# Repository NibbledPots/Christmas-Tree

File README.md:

# Christmas-Tree
Fun christmas tree PCB ornament with LEDs
* Base is roughly 5cm and its about 6.5cm tall
* Has a nice hole in it to make it an ornament

Used to be series, turns out that doesn't work so now its parallel. I don't really know how to nicely route parallel circuits so it looks ugly and **might not work**, maybe I'll try again next christmas

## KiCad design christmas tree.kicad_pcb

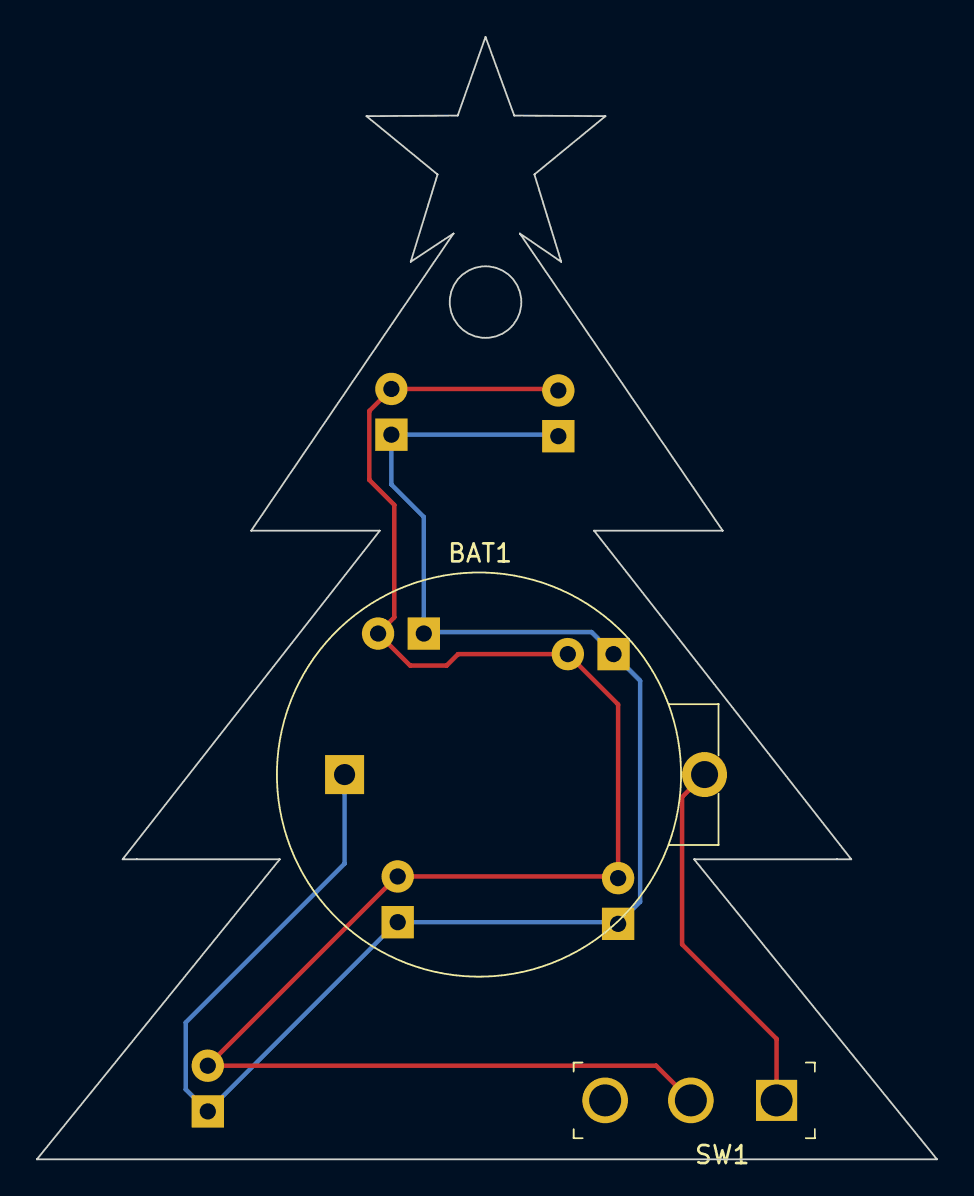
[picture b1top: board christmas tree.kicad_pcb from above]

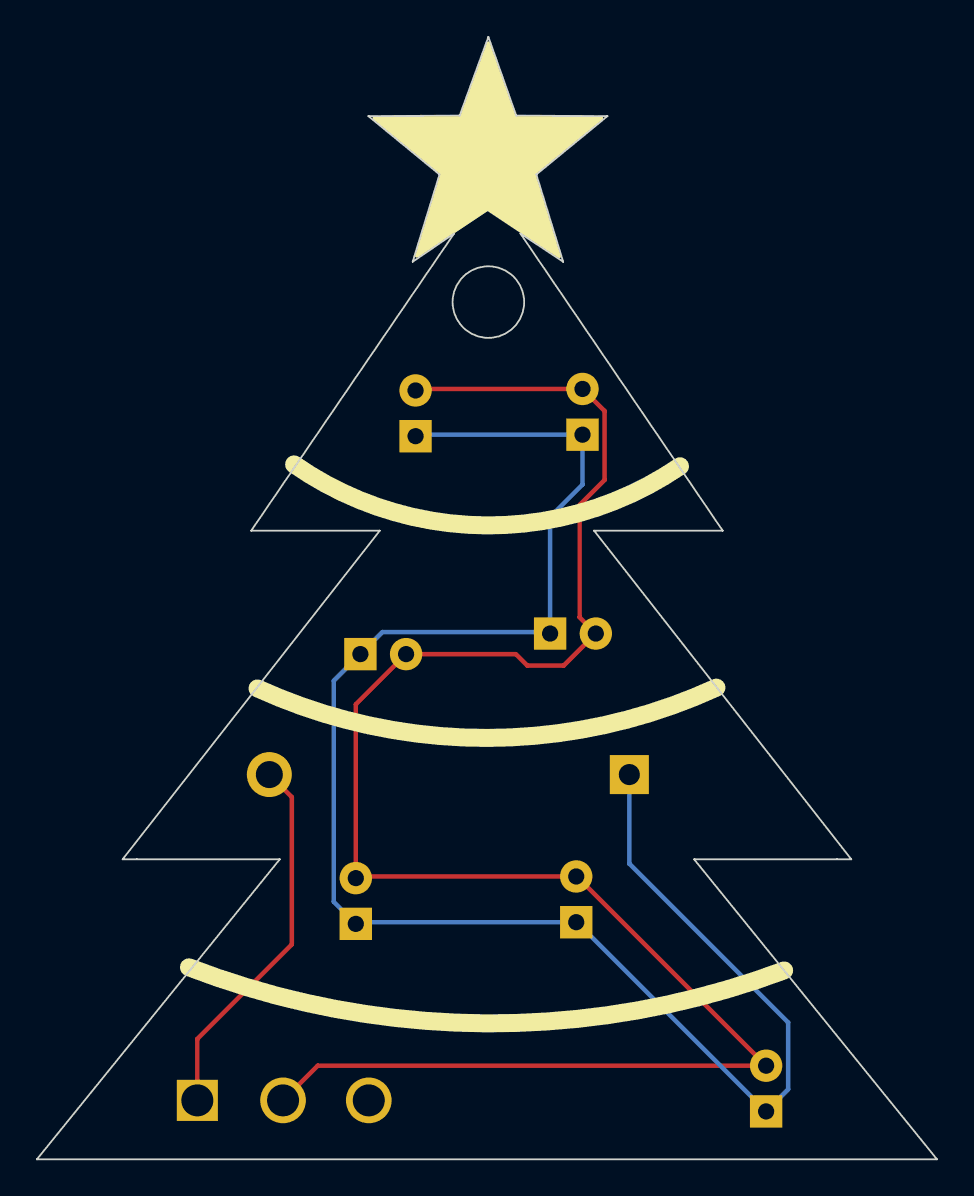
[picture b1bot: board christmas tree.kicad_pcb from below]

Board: 2 copper layers, 50.0 x 62.4 mm, 9 parts (7 on the bottom side), 3 nets.

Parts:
BAT1: BS-7; Battery_Holder_Coin_2032_BS-7
D1, D2, D3, D4, D6, D7: LED; LED_D5.0mm
Dr: LED; LED_D5.0mm
SW1: SW_SPST; Switch_Slide_11.6x4mm_EG1218

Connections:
unnamed: BAT1.Neg, D1.1 (K), D2.1 (K), D3.1 (K), D4.1 (K), D6.1 (K), D7.1 (K), Dr.1 (K)
unnamed: BAT1.Pos, SW1.1 (A)
unnamed: D1.2 (A), D2.2 (A), D3.2 (A), D4.2 (A), D6.2 (A), D7.2 (A), Dr.2 (A), SW1.2 (B)

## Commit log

2022-12-07 add submodule
2022-12-07 made schematic and edge cuts
2022-12-07 added components, and deco
2022-12-08 added gerbers
2022-12-29 Parallelized schematic
2022-12-29 messy routing but might work
2022-12-29 Made a README
2023-01-01 retraced the circuit
    still don't know if this will work
2023-11-24 Sized switch
2023-11-27 gerbers
